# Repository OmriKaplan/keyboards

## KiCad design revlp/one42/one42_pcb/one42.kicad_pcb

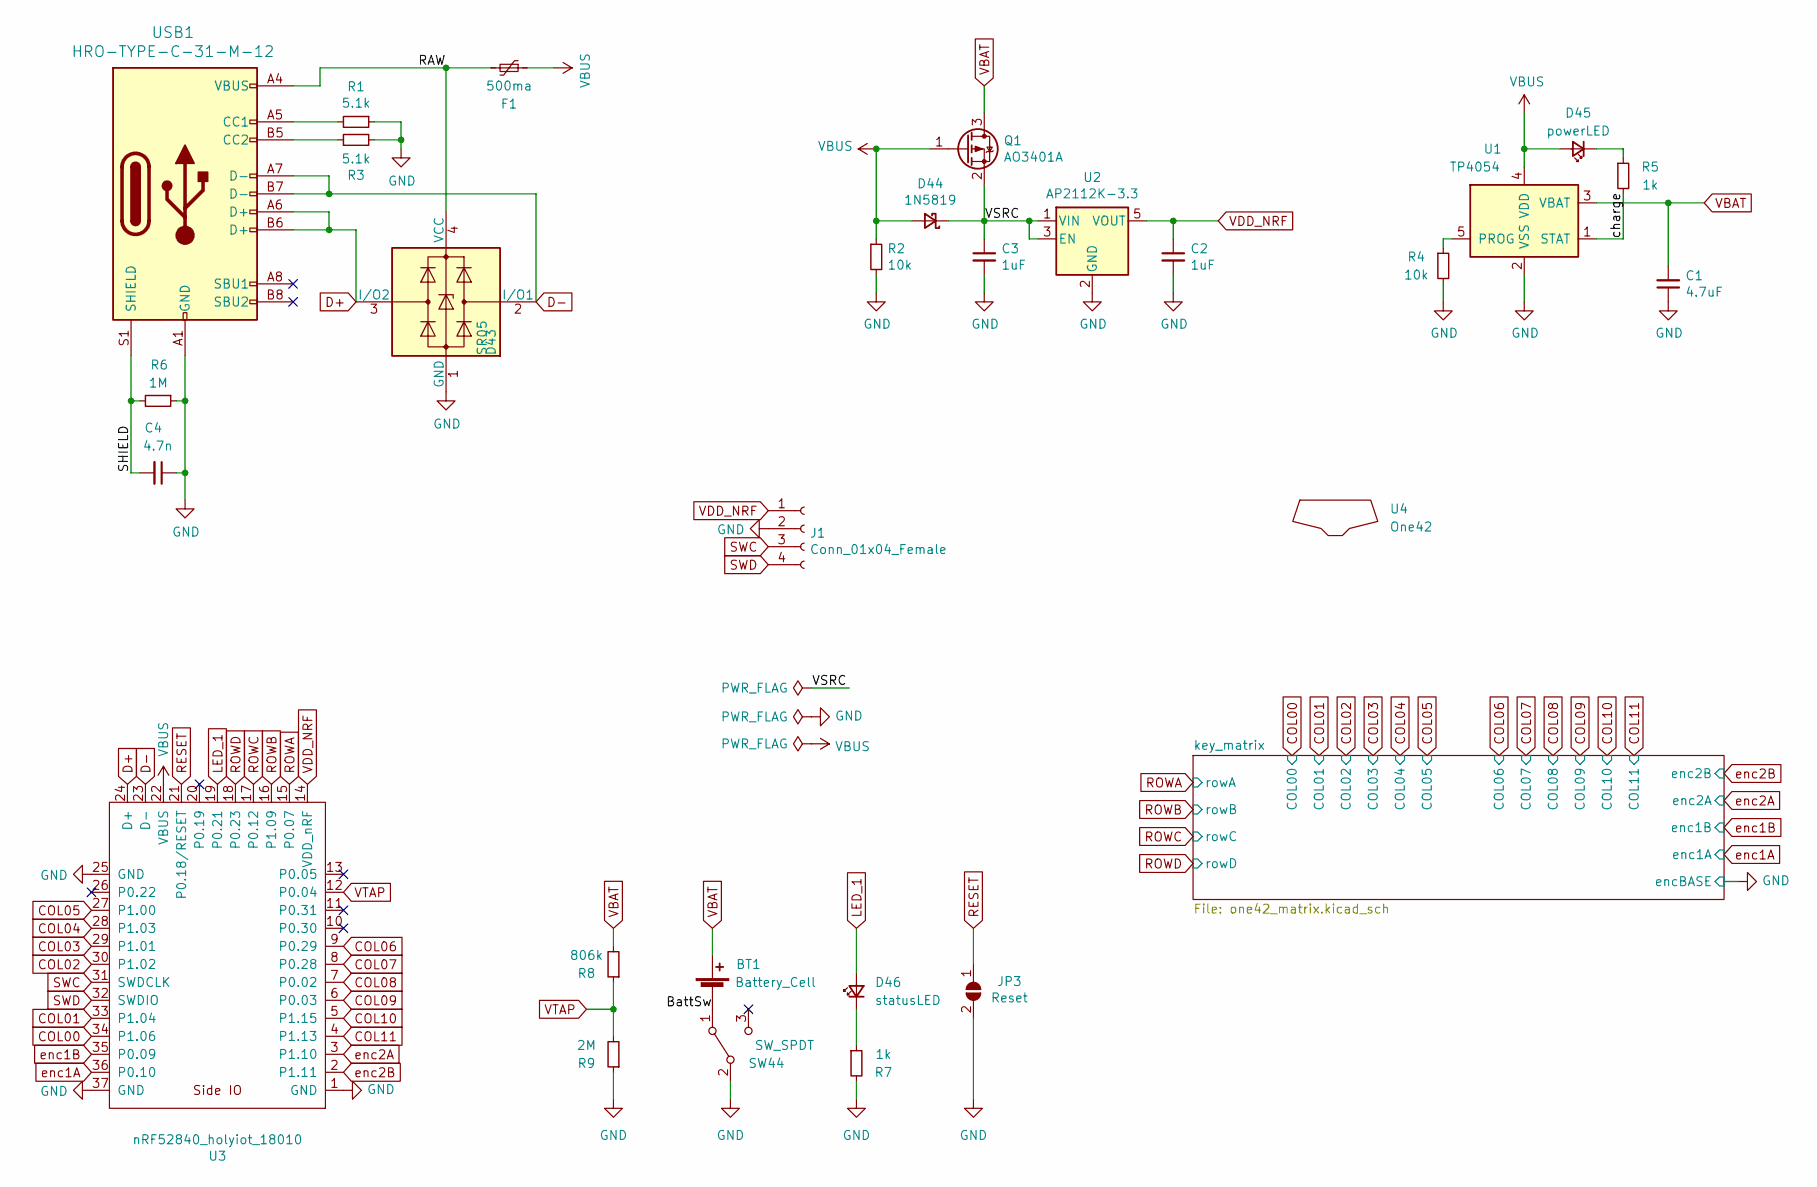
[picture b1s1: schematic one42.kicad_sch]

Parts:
BT1: Battery_Cell; cell_pads
C1: 4.7uF; C_0805_2012Metric; JLC 0805
C2, C3: 1uF; C_0805_2012Metric; JLC 0805
C4: 4.7n; C_1206_3216Metric
D43: SR05; SOT-143
D44: 1N5819; D_SOD-123
D45: powerLED; D_0805_2012Metric
D46: statusLED; D_0805_2012Metric
F1: 500ma; Fuse_1206_3216Metric
J1: Conn_01x04_Female; PinHeader_1x04_P2.54mm_Vertical
JP3: Reset; SolderJumper-2_P1.3mm_Open_RoundedPad1.0x1.5mm
Q1: AO3401A; SOT-23; JLC SOT-23-3L
R1, R3: 5.1k; R_0805_2012Metric; JLC 0805
R2, R4: 10k; R_0805_2012Metric; JLC 0805
R5, R7: 1k; R_0805_2012Metric; JLC 0805
R6: 1M; R_0805_2012Metric; JLC 0805
R8: 806k; R_0805_2012Metric
R9: 2M; R_0805_2012Metric; JLC 0805
SW44: SW_SPDT; switch_SSSS811101
U1: TP4054; SOT-23-5; JLC SOT-23-5
U2: AP2112K-3.3; SOT-23-5
U3: nRF52840_holyiot_18010; nRF52840_holyiot_18010_HS_simple
U4: One42; one42
USB1: HRO-TYPE-C-31-M-12; USB_C_Receptacle_HRO_TYPE-C-31-M-12_handsolder

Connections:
/BattSw: BT1.2 (-), SW44.1 (A)
/RAW: D43.4 (VCC), F1.2, USB1.A4 (VBUS), USB1.A9 (VBUS), USB1.B4 (VBUS), USB1.B9 (VBUS)
/SHIELD: C4.2, R6.2, USB1.S1 (SHIELD)
/VSRC: C3.1, D44.1 (K), Q1.2 (S), U2.1 (VIN), U2.3 (EN)
/charge: R5.2, U1.1 (STAT)
COL00: U3.34 (P1.06); also elsewhere on the board
COL01: U3.33 (P1.04); also elsewhere on the board
COL02: U3.30 (P1.02); also elsewhere on the board
COL03: U3.29 (P1.01); also elsewhere on the board
COL04: U3.28 (P1.03); also elsewhere on the board
COL05: U3.27 (P1.00); also elsewhere on the board
COL08: U3.7 (P0.02); also elsewhere on the board
COL09: U3.6 (P0.03); also elsewhere on the board
COL10: U3.5 (P1.15); also elsewhere on the board
COL11: U3.4 (P1.13); also elsewhere on the board
D+: D43.3 (I/O2), U3.24 (D+), USB1.A6 (D+), USB1.B6 (D+)
D-: D43.2 (I/O1), U3.23 (D-), USB1.A7 (D-), USB1.B7 (D-)
GND: C1.1, C2.2, C3.2, C4.1, D43.1 (GND), J1.2, JP3.2 (B), R1.1, R2.2, R3.2, R4.2, R6.1, R7.2, R9.1, SW44.2 (B), U1.2 (VSS), U2.2 (GND), U3.1 (GND), U3.25 (GND), U3.37 (GND), USB1.A1 (GND), USB1.A12 (GND), USB1.B1 (GND), USB1.B12 (GND); also elsewhere on the board
LED_1: D46.2 (A), U3.19 (P0.21)
unnamed: D45.1 (K), R5.1
unnamed: D46.1 (K), R7.1
unnamed: R1.2, USB1.A5 (CC1)
unnamed: R3.1, USB1.B5 (CC2)
unnamed: R4.1, U1.5 (PROG)
RESET: JP3.1 (A), U3.21 (P0.18/RESET)
ROWA: U3.15 (P0.07); also elsewhere on the board
ROWB: U3.16 (P1.09); also elsewhere on the board
ROWC: U3.17 (P0.12); also elsewhere on the board
ROWD: U3.18 (P0.23); also elsewhere on the board
SWC: J1.3, U3.31 (SWDCLK)
SWD: J1.4, U3.32 (SWDIO)
VBAT: BT1.1 (+), C1.2, Q1.3 (D), R8.2, U1.3 (VBAT)
VBUS: D44.2 (A), D45.2 (A), F1.1, Q1.1 (G), R2.1, U1.4 (VDD), U3.22 (VBUS)
VDD_NRF: C2.1, J1.1, U2.5 (VOUT), U3.14 (VDD_nRF)
VTAP: R8.1, R9.2, U3.12 (P0.04)
enc1A: U3.36 (P0.10); also elsewhere on the board
enc1B: U3.35 (P0.09); also elsewhere on the board
enc2A: U3.3 (P1.10); also elsewhere on the board
enc2B: U3.2 (P1.11); also elsewhere on the board

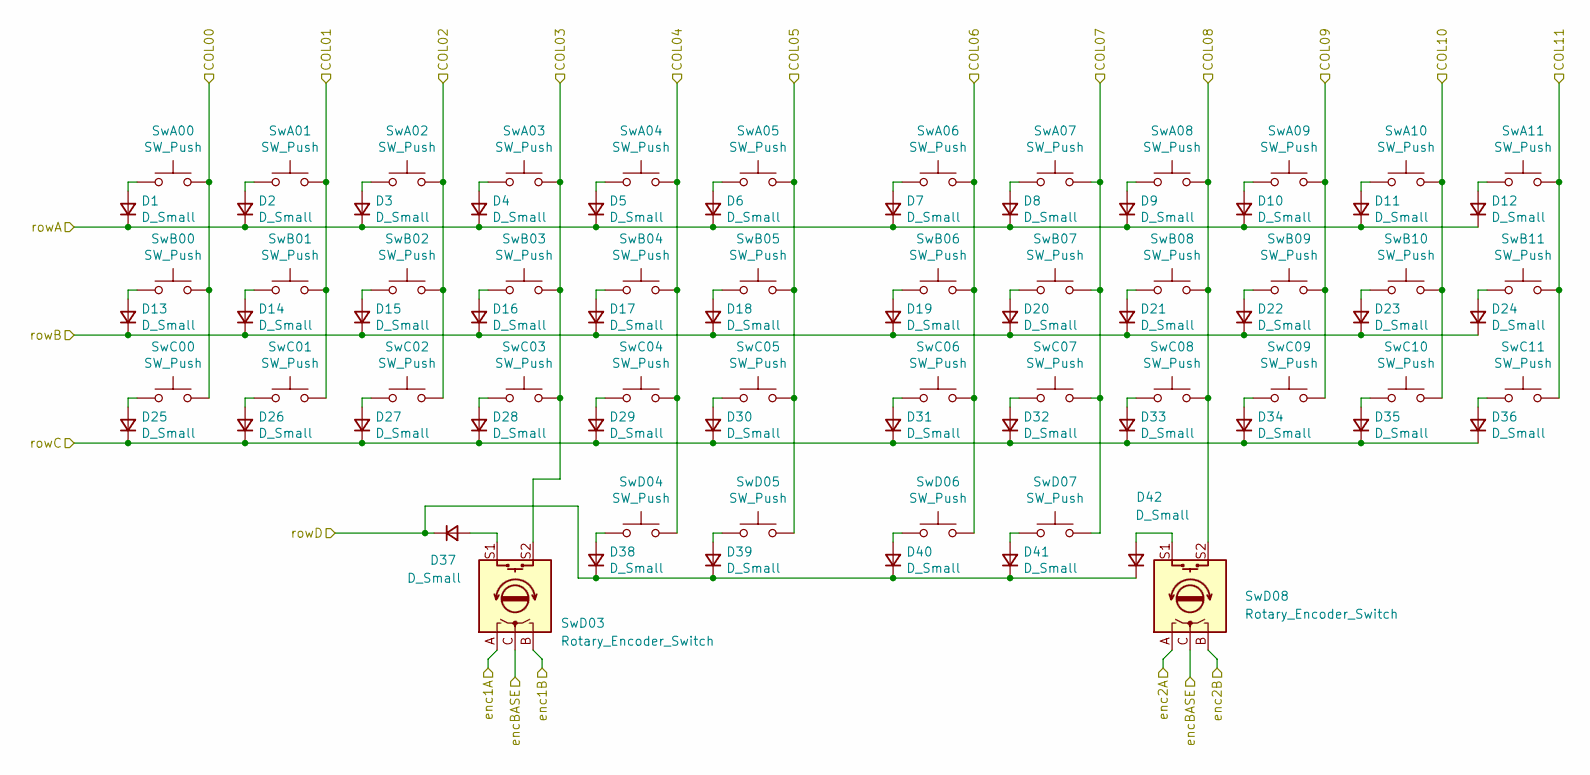
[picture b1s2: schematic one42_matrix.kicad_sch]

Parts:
D1, D2, D3, D4, D5, D6, D7, D8, D9, D10, D11, D12, D13, D14, D15, D16, D17, D18, D19, D20, D21, D22, D23, D24, D25, D26, D27, D28, D29, D30, D31, D32, D33, D34, D35, D36, D37, D38, D39, D40, D41, D42: D_Small; D_SOD-123; JLC SOD-123
SwA00, SwA01, SwA02, SwA03, SwA04, SwA05, SwA06, SwA07, SwA08, SwA09, SwA10, SwA11: SW_Push; pg1353
SwB00, SwB01, SwB02, SwB03, SwB04, SwB05, SwB06, SwB07, SwB08, SwB09, SwB10, SwB11: SW_Push; pg1353
SwC00, SwC01, SwC02, SwC03, SwC04, SwC05, SwC06, SwC07, SwC08, SwC09, SwC10, SwC11: SW_Push; pg1353
SwD03, SwD08: Rotary_Encoder_Switch; pg1353_ec11rotSw
SwD04, SwD05, SwD06, SwD07: SW_Push; pg1353

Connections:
COL00: SwA00.2, SwB00.2, SwC00.2; also elsewhere on the board
COL01: SwA01.2, SwB01.2, SwC01.2; also elsewhere on the board
COL02: SwA02.2, SwB02.2, SwC02.2; also elsewhere on the board
COL03: SwA03.2, SwB03.2, SwC03.2, SwD03.S2; also elsewhere on the board
COL04: SwA04.2, SwB04.2, SwC04.2, SwD04.2; also elsewhere on the board
COL05: SwA05.2, SwB05.2, SwC05.2, SwD05.2; also elsewhere on the board
COL08: SwA08.2, SwB08.2, SwC08.2, SwD08.S2; also elsewhere on the board
COL09: SwA09.2, SwB09.2, SwC09.2; also elsewhere on the board
COL10: SwA10.2, SwB10.2, SwC10.2; also elsewhere on the board
COL11: SwA11.2, SwB11.2, SwC11.2; also elsewhere on the board
GND: SwD03.C, SwD08.C; also elsewhere on the board
unnamed: D1.2 (A), SwA00.1
unnamed: D2.2 (A), SwA01.1
unnamed: D3.2 (A), SwA02.1
unnamed: D4.2 (A), SwA03.1
unnamed: D5.2 (A), SwA04.1
unnamed: D6.2 (A), SwA05.1
unnamed: D7.2 (A), SwA06.1
unnamed: D8.2 (A), SwA07.1
unnamed: D9.2 (A), SwA08.1
unnamed: D10.2 (A), SwA09.1
unnamed: D11.2 (A), SwA10.1
unnamed: D12.2 (A), SwA11.1
unnamed: D13.2 (A), SwB00.1
unnamed: D14.2 (A), SwB01.1
unnamed: D15.2 (A), SwB02.1
unnamed: D16.2 (A), SwB03.1
unnamed: D17.2 (A), SwB04.1
unnamed: D18.2 (A), SwB05.1
unnamed: D19.2 (A), SwB06.1
unnamed: D20.2 (A), SwB07.1
unnamed: D21.2 (A), SwB08.1
unnamed: D22.2 (A), SwB09.1
unnamed: D23.2 (A), SwB10.1
unnamed: D24.2 (A), SwB11.1
unnamed: D25.2 (A), SwC00.1
unnamed: D26.2 (A), SwC01.1
unnamed: D27.2 (A), SwC02.1
unnamed: D28.2 (A), SwC03.1
unnamed: D29.2 (A), SwC04.1
unnamed: D30.2 (A), SwC05.1
unnamed: D31.2 (A), SwC06.1
unnamed: D32.2 (A), SwC07.1
unnamed: D33.2 (A), SwC08.1
unnamed: D34.2 (A), SwC09.1
unnamed: D35.2 (A), SwC10.1
unnamed: D36.2 (A), SwC11.1
unnamed: D37.2 (A), SwD03.S1
unnamed: D38.2 (A), SwD04.1
unnamed: D39.2 (A), SwD05.1
unnamed: D42.2 (A), SwD08.S1
ROWA: D1.1 (K), D2.1 (K), D3.1 (K), D4.1 (K), D5.1 (K), D6.1 (K), D7.1 (K), D8.1 (K), D9.1 (K), D10.1 (K), D11.1 (K), D12.1 (K); also elsewhere on the board
ROWB: D13.1 (K), D14.1 (K), D15.1 (K), D16.1 (K), D17.1 (K), D18.1 (K), D19.1 (K), D20.1 (K), D21.1 (K), D22.1 (K), D23.1 (K), D24.1 (K); also elsewhere on the board
ROWC: D25.1 (K), D26.1 (K), D27.1 (K), D28.1 (K), D29.1 (K), D30.1 (K), D31.1 (K), D32.1 (K), D33.1 (K), D34.1 (K), D35.1 (K), D36.1 (K); also elsewhere on the board
ROWD: D37.1 (K), D38.1 (K), D39.1 (K), D40.1 (K), D41.1 (K), D42.1 (K); also elsewhere on the board
enc1A: SwD03.A; also elsewhere on the board
enc1B: SwD03.B; also elsewhere on the board
enc2A: SwD08.A; also elsewhere on the board
enc2B: SwD08.B; also elsewhere on the board

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
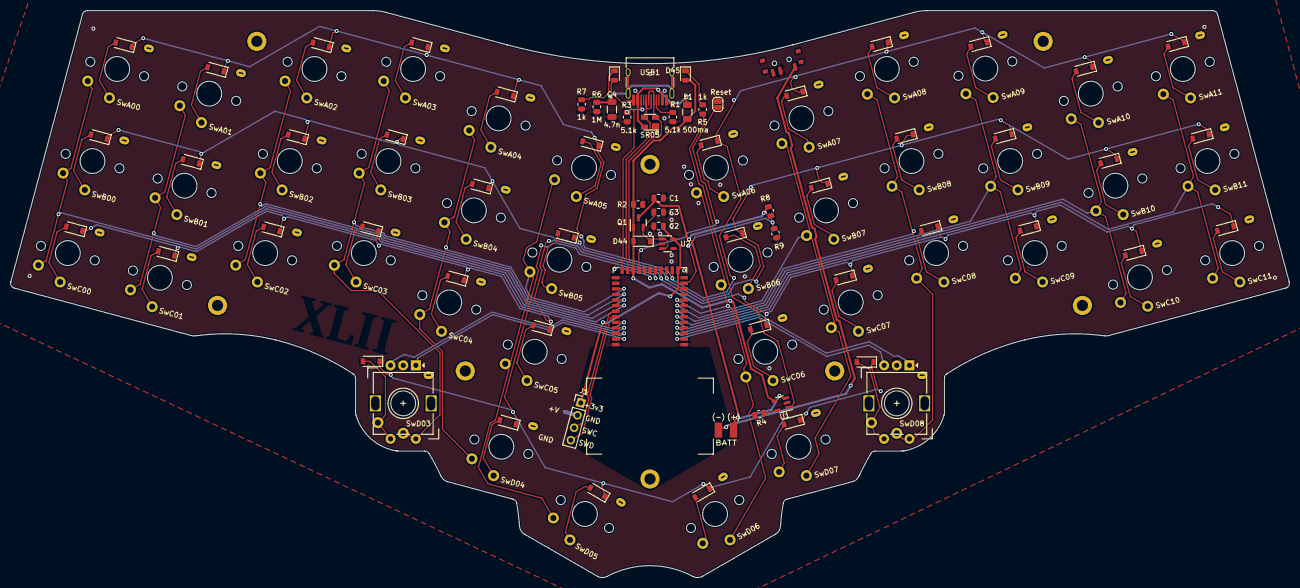
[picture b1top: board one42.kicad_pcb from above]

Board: 2 copper layers, 252.3 x 111.8 mm, 112 parts (0 on the bottom side), 83 nets.

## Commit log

2021-09-22 [kicad] Add component: Holyiot-18010
2021-09-23 [kicad] Add component: USB-C connector
    Per aio3:
    https://wiki.ai03.com/books/pcb-design/page/list-of-kicad-keyboard-parts-libraries
2021-09-28 [keyboard] Introduce one42
2021-10-11 Update kicad libs: Additions for One42
2021-10-20 [keyboard] One42: Long Live Ahokore!
2021-11-14 [keyboard] One42: Version 1.0
